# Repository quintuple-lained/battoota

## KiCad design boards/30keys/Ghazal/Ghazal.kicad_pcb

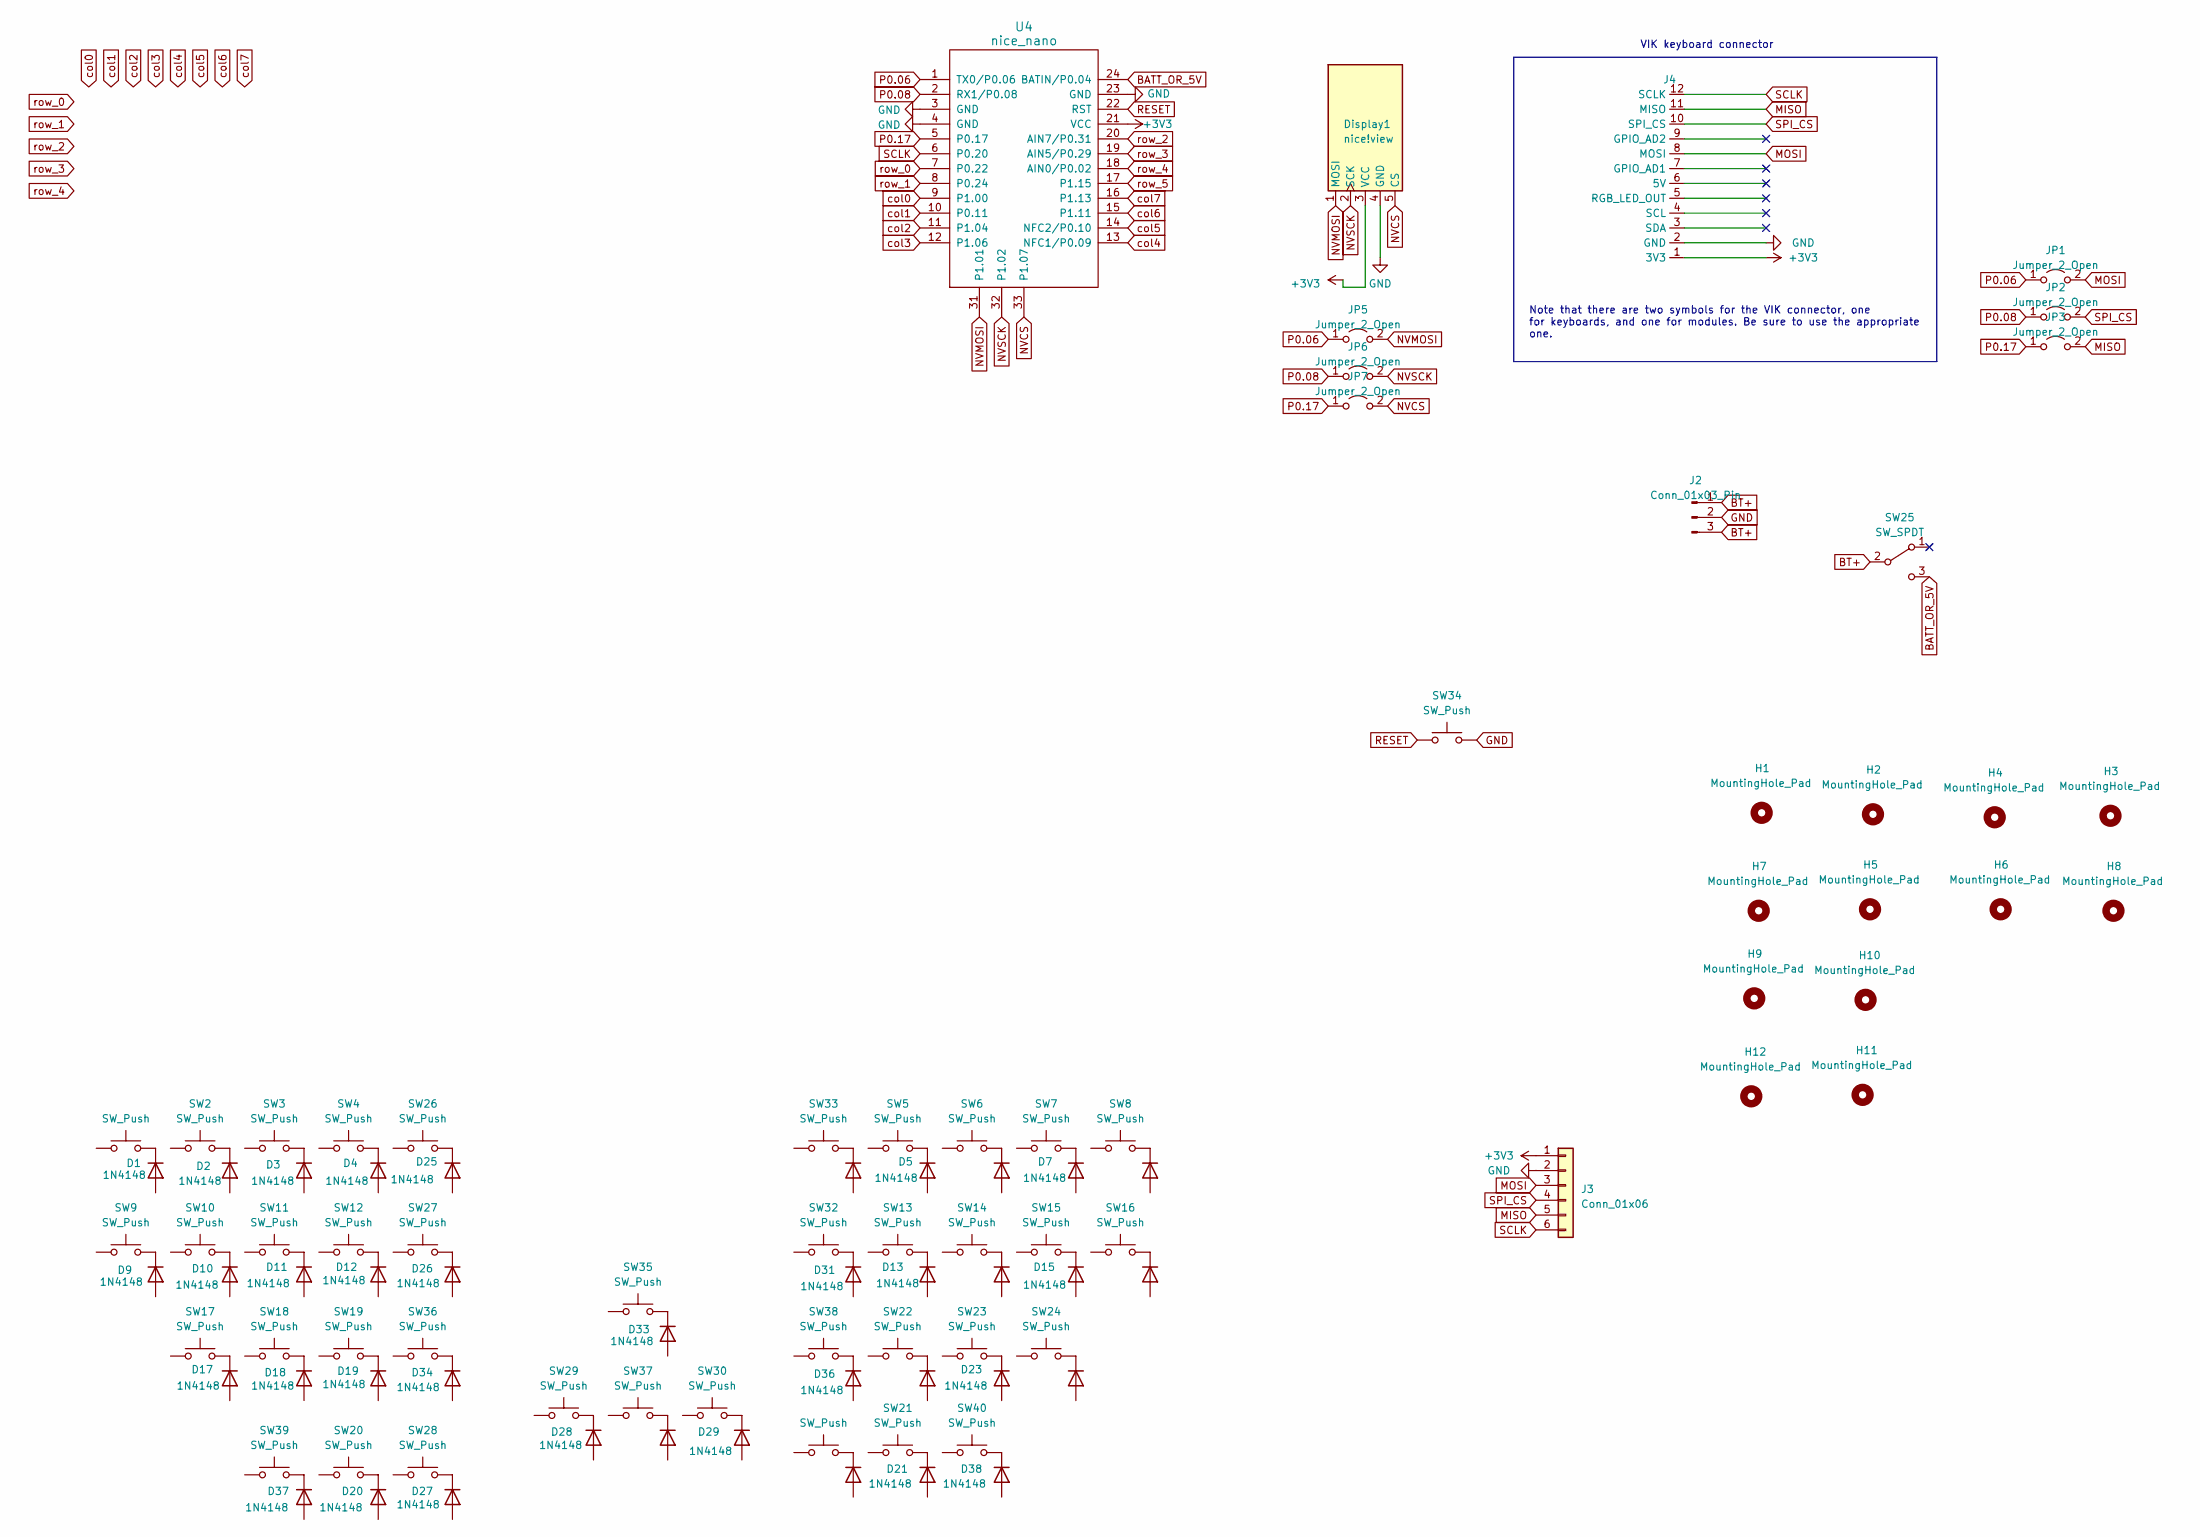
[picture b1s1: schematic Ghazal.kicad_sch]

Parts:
D1, D2, D3, D4, D5, D6, D7, D8, D9, D10, D11, D12, D13, D14, D15, D16, D17, D18, D19, D20, D21, D22, D23, D24, D25, D26, D27, D28, D29, D30, D31, D32, D33, D34, D35, D36, D37, D38: 1N4148; D_SOD-123; LCSC C8598
Display1: nice!view; nice_view
H1, H2, H3, H4, H5, H6, H7, H8, H9, H10, H11, H12: MountingHole_Pad; MountingHole_M3
J2: Conn_01x03_Pin; 3JST_BAT
J3: Conn_01x06; PinHeader_1x06_P2.54mm_Vertical
J4: vik-keyboard-connector-horizontal; LCSC C479750
JP1, JP2, JP3, JP5, JP6, JP7: Jumper_2_Open; SolderJumper-2_P1.3mm_Open_TrianglePad1.0x1.5mm
SW1, SW2, SW3, SW4, SW5, SW6, SW7, SW8, SW9, SW10, SW11, SW12, SW13, SW14, SW15, SW16, SW17, SW18, SW19, SW20, SW21, SW22, SW23, SW24, SW26, SW27, SW28, SW29, SW30, SW31, SW32, SW33, SW35, SW36, SW37, SW38, SW39, SW40: SW_Push; Kailh_hotswap_only_MX-CHOC
SW25: SW_SPDT; SW_CuK_OS102011MA1QN1_SPDT_Angled
SW34: SW_Push; ResetSW
U4: nice_nano

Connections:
+3V3: Display1.3 (VCC), J3.1; also elsewhere on the board
BATT_OR_5V: SW25.3 (C); also elsewhere on the board
BT+: J2.1, J2.3, SW25.2 (B)
GND: Display1.4 (GND), J2.2, J3.2, SW34.2; also elsewhere on the board
MISO: J3.5, JP3.2 (B); also elsewhere on the board
MOSI: J3.3, JP1.2 (B); also elsewhere on the board
NVCS: Display1.5 (CS), JP7.2 (B); also elsewhere on the board
NVMOSI: Display1.1 (MOSI), JP5.2 (B); also elsewhere on the board
NVSCK: Display1.2 (SCK), JP6.2 (B); also elsewhere on the board
unnamed: D1.1 (K), SW1.2
unnamed: D2.1 (K), SW2.2
unnamed: D3.1 (K), SW3.2
unnamed: D4.1 (K), SW4.2
unnamed: D5.1 (K), SW5.2
unnamed: D6.1 (K), SW6.2
unnamed: D7.1 (K), SW7.2
unnamed: D8.1 (K), SW8.2
unnamed: D9.1 (K), SW9.2
unnamed: D10.1 (K), SW10.2
unnamed: D11.1 (K), SW11.2
unnamed: D12.1 (K), SW12.2
unnamed: D13.1 (K), SW13.2
unnamed: D14.1 (K), SW14.2
unnamed: D15.1 (K), SW15.2
unnamed: D16.1 (K), SW16.2
unnamed: D17.1 (K), SW17.2
unnamed: D18.1 (K), SW18.2
unnamed: D19.1 (K), SW19.2
unnamed: D20.1 (K), SW20.2
unnamed: D21.1 (K), SW21.2
unnamed: D22.1 (K), SW22.2
unnamed: D23.1 (K), SW23.2
unnamed: D24.1 (K), SW24.2
unnamed: D25.1 (K), SW26.2
unnamed: D27.1 (K), SW28.2
unnamed: D28.1 (K), SW29.2
unnamed: D29.1 (K), SW30.2
unnamed: D30.1 (K), SW31.2
unnamed 39: D31.1 (K), SW32.2; also elsewhere on the board
unnamed: D32.1 (K), SW33.2
unnamed: D33.1 (K), SW35.2
unnamed: D34.1 (K), SW36.2
unnamed: D35.1 (K), SW37.2
unnamed: D36.1 (K), SW38.2
unnamed: D37.1 (K), SW39.2
unnamed: D38.1 (K), SW40.2
P0.06: JP1.1 (A), JP5.1 (A); also elsewhere on the board
P0.08: JP2.1 (A), JP6.1 (A); also elsewhere on the board
P0.17: JP3.1 (A), JP7.1 (A); also elsewhere on the board
RESET: SW34.1; also elsewhere on the board
SCLK: J3.6; also elsewhere on the board
SPI_CS: J3.4, JP2.2 (B); also elsewhere on the board

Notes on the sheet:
Note that there are two symbols for the VIK connector, one for keyboards, and one for modules. Be sure to use the appropriate one.
VIK keyboard connector

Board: 2 copper layers, 102 parts (44 on the bottom side), 49 nets, no tracks yet.

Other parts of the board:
D26#2, D31#2: 1N4148; D_SOD-123
J1: vik-keyboard-connector-horizontal
SW20#2, SW27#2, SW32#2: SW_Push; Kailh_hotswap_only_MX-CHOC
U1: nice_nano

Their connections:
+3V3: J1.1 (3V3), U1.21 (VCC); also elsewhere on the board
BATT_OR_5V: U1.24 (BATIN/P0.04); also elsewhere on the board
GND: J1.2 (GND), U1.3 (GND), U1.4 (GND), U1.23 (GND); also elsewhere on the board
MISO: J1.11 (MISO); also elsewhere on the board
MOSI: J1.8 (MOSI); also elsewhere on the board
NVCS: U1.33 (P1.07); also elsewhere on the board
NVMOSI: U1.31 (P1.01); also elsewhere on the board
NVSCK: U1.32 (P1.02); also elsewhere on the board
unnamed: D26#2.1 (K), SW27#2.2
unnamed 39: D31#2.1 (K), SW32#2.2; also elsewhere on the board
P0.06: U1.1 (TX0/P0.06); also elsewhere on the board
P0.08: U1.2 (RX1/P0.08); also elsewhere on the board
P0.17: U1.5 (P0.17); also elsewhere on the board
RESET: U1.22 (RST); also elsewhere on the board
SCLK: J1.12 (SCLK), U1.6 (P0.20); also elsewhere on the board
SPI_CS: J1.10 (SPI_CS); also elsewhere on the board
